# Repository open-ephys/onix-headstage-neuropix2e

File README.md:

# ONIX Neuropixels 2.0 Headstage

Serialized, multifunction ONIX headstage for IMEC Neuropixels-2.0 probes

**Features**
- 2x [Neuropixels 2.0](https://www.neuropixels.org/) probes per headstage
- Integrated absolute orientation tracking
- Single, 0.3 mm diameter micro-coaxial tether
- Torque-free commutation when used with an [ONIX Commutator](https://github.com/open-ephys/onix-commutator)
- 0.64 grams

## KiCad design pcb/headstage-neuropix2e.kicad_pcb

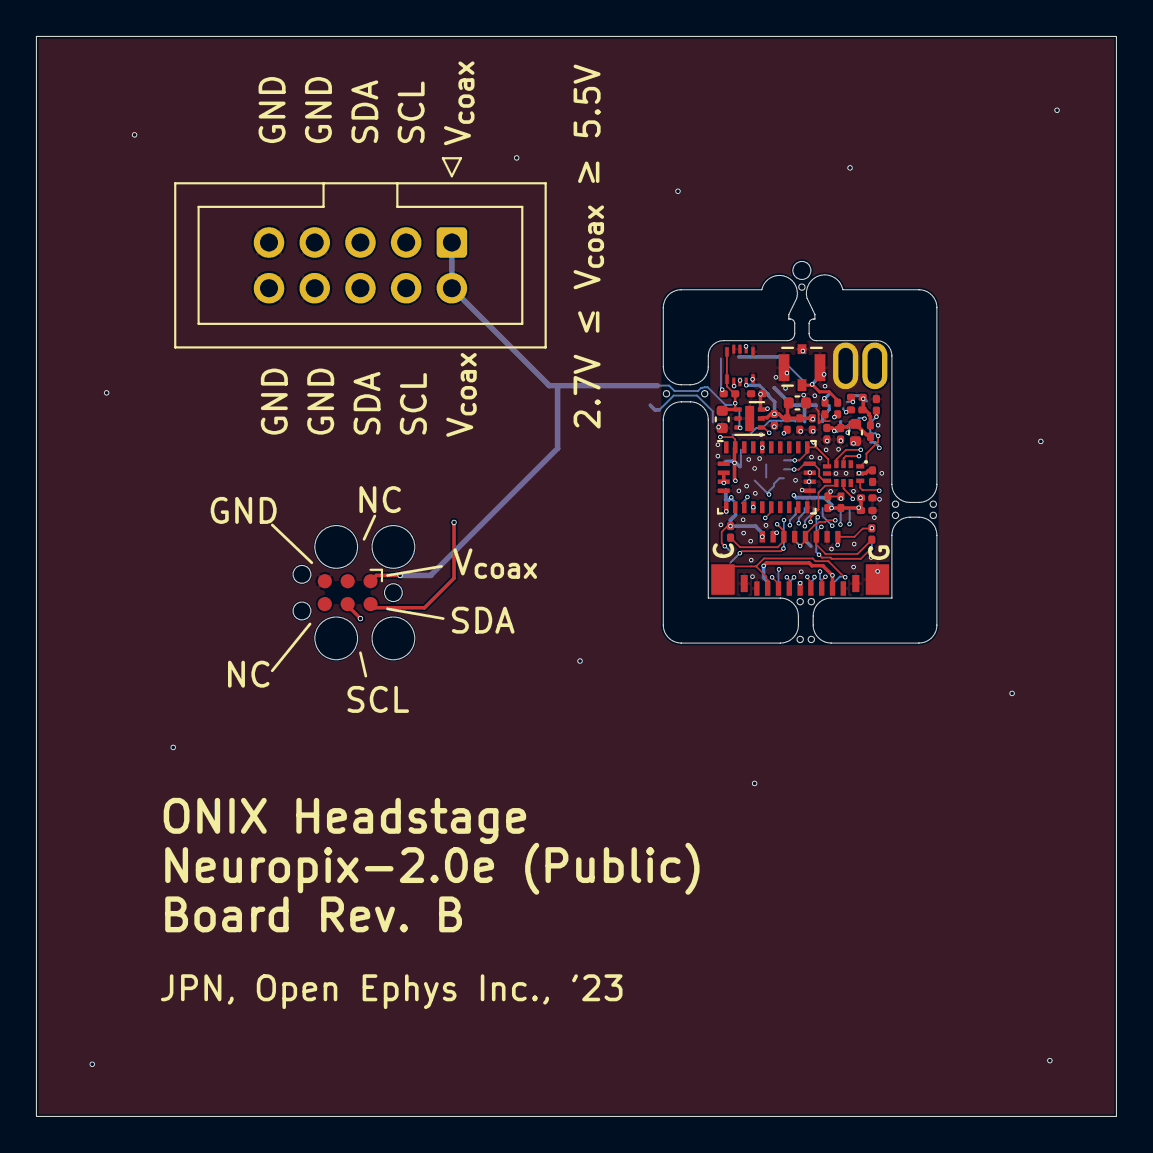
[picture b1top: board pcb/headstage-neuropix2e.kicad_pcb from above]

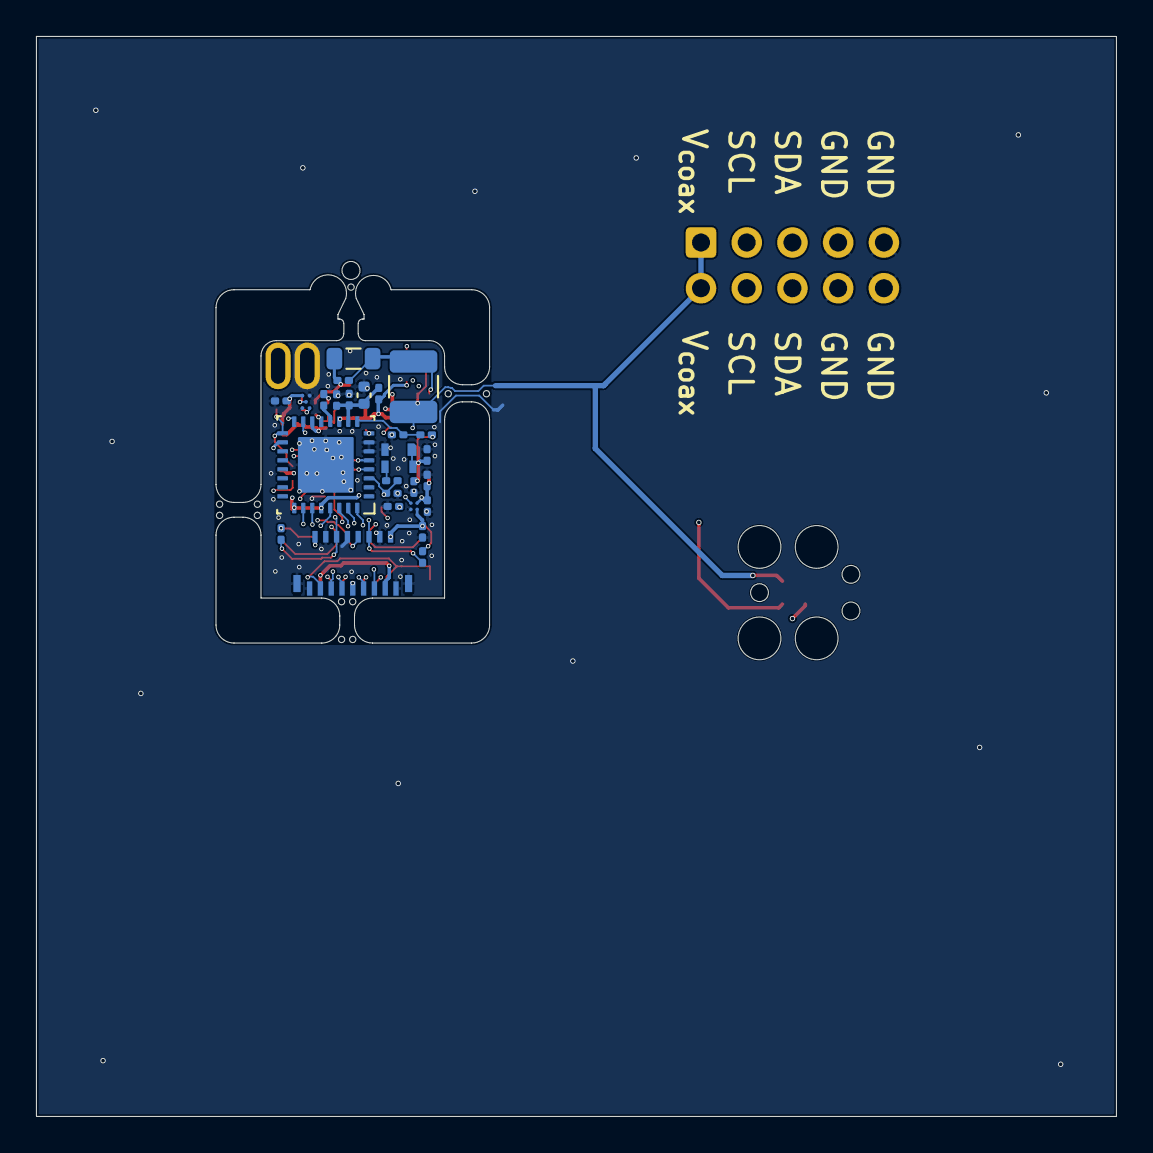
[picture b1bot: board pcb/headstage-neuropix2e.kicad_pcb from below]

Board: 4 copper layers, 60.0 x 60.0 mm, 62 parts (26 on the bottom side), 35 nets.

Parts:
C1, C2, C4, C5, C21: 1uF; C_0201_0603Metric
C3, C12, C15, C18: 10uF; C_0402_1005Metric
C6, C8, C10, C13, C16, C23: 10nF; C_0201_0603Metric
C7, C9, C11, C14, C17, C19, C22, C25, C26, C27, C28: 0.1uF; C_0201_0603Metric
C20: 47nF; C_0201_0603Metric
C24: 27pF; C_0201_0603Metric
J1: X.FL-R-SMT-1(02); HIROSE_X.FL-R-SMT-1
J2, J3: FH35C-17S-0.3SHW(99); HIROSE_FH35C-17S-0.3SHW(99)
J4: SBH11-PBPC-D05-ST-BK; IDC-Header_2x05_P2.54mm_Vertical
J5: TC2030; Tag-Connect_TC2030-IDC-FP_2x03_P1.27mm_Vertical
J6: 050700622; MOLEX_5050700622
L1: CBC3225T101MR; L_1210_3225Metric
L2: ASMPH-0805-4R7M-T; L_0805_2012Metric
L3, L4: BLF03RD501GZED; L_0201_0603Metric
R1, R2: 1k; R_0201_0603Metric
R3, R4: 2k; R_0201_0603Metric
R5, R6, R7, R9, R10, R11, R12: 10k; R_0201_0603Metric
R8: 49.9; R_0201_0603Metric
R13: 10; R_0201_0603Metric
TP1: GND; OE_TP-Oval-2.8x1.6mm
TP2: NP_{Lesion}; OE_TP-Oval-2.8x1.6mm
TP3: NP_{Cal}; TestPoint_Pad_1.3x1.7mm_Tight
TP4: NP_{TP1}; TestPoint_Pad_1.3x1.7mm_Tight
U1: MIC5335-JGYMT; MICROCHIP_TDFN-6-1EP_1.6x1.6mm_P0.5mm_EP0.5x1.4mm
U2: NCP163AFCT180T2G; ONSEMI_567JZ_WLCSP4-0.64x0.64
U3: DS90UB933TRTVTQ1; TI_RTV0032A
U4: STG3856; ST_QFN12L_2.2x1.4x0.55mm_P0.4mm
U5: ECS-2016MV-480-CN-TR; MICROCHIP_VFLGA4-2.0x1.6
U6: M24C64-FCS6TP/K; ST_WLCSP5-0.959x1.073
U7: BNO055; LGA-28_5.2x3.8mm_P0.5mm

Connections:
+1.8VA: C4.1, J2.2, J2.3, J2.16, J3.2, J3.3, J3.16, R9.1, R10.1, R11.1, R12.1, U2.A2 (VOUT)
+1V8: C1.1, C6.1, C7.1, C8.1, C9.1, C13.1, C14.1, C15.1, C22.1, C23.1, C25.2, C27.2, J6.5, L3.2, L4.2, R1.1, R2.1, R6.1, R7.1, U1.5 (VOUT2), U3.11 (VDDT), U3.25 (VDDIO), U3.28 (VDDD), U4.11 (VCC), U5.1 (EN), U5.4 (VCC), U6.A1 (VCC), U7.28 (VDDIO)
+2V5: C2.1, C5.1, C26.2, J6.6, U1.6 (VOUT1), U2.A1 (VIN), U7.3 (VDD), U7.4 (~BOOT_LOAD_PIN), U7.11 (~RESET)
+4V: C3.1, J4.1, J4.2, J5.1 (VCC), J6.MP1 (MountPin1), J6.MP2 (MountPin2), L1.1, R3.1, U1.1 (VIN), U1.3 (EN2), U1.4 (EN1)
/DC Tap & Regulation/RF+DC: C19.2, J1.1 (In), L2.1, R4.2
/DC Tap & Regulation/VDDA_{EN}: U2.B1 (EN), U3.15 (GPIO0)
/Neuropixels 2.0/D0_{A}: J2.5, U3.26 (DIN_6)
/Neuropixels 2.0/D0_{B}: J3.5, U3.32 (DIN_11)
/Neuropixels 2.0/D1_{A}: J2.11, U3.31 (DIN_10)
/Neuropixels 2.0/D1_{B}: J3.11, U3.27 (DIN_7)
/Neuropixels 2.0/D2_{A}: J2.7, U3.29 (DIN_8)
/Neuropixels 2.0/D2_{B}: J3.7, U3.30 (DIN_9)
/Neuropixels 2.0/NP_{Cal}: J2.15, J3.15, TP3.1
/Neuropixels 2.0/NP_{Lesion}: J2.13, J3.13, TP2.1
/Neuropixels 2.0/NP_{Sel0}: R5.1, U3.17 (GPIO2/CLK0), U4.12 (IN1)
/Neuropixels 2.0/NP_{Sel1}: U3.18 (GPIO3/CLKIN), U4.10 (IN2)
/Neuropixels 2.0/NP_{~RST}: J2.8, J3.8, U3.16 (GPIO1)
/Neuropixels 2.0/PCLK: C24.1, J2.9, J3.9, R13.2, U3.3 (PCLK)
/Neuropixels 2.0/SCL: J4.3, J4.4, J5.4 (SWCLK), J6.1, R2.2, U3.4 (SCL), U4.6 (D2), U6.C3 (SCL), U7.19 (COM1)
/Neuropixels 2.0/SCL_{A}: J2.6, R11.2, U4.8 (2S2)
/Neuropixels 2.0/SCL_{B}: J3.6, R12.2, U4.7 (2S3)
/Neuropixels 2.0/SDA: J4.5, J4.6, J5.2 (SWDIO), J6.3, R1.2, U3.5 (SDA), U4.4 (D1), U6.B2 (SDA), U7.20 (COM0)
/Neuropixels 2.0/SDA_{A}: J2.12, R9.2, U4.2 (1S2)
/Neuropixels 2.0/SDA_{B}: J3.12, R10.2, U4.3 (1S3)
/Serializer/Dout-: C20.2, R8.1
GND: C1.2, C2.2, C3.2, C4.2, C5.2, C6.2, C7.2, C8.2, C9.2, C10.2, C11.2, C12.2, C13.2, C14.2, C15.2, C16.2, C17.2, C18.2, C21.2, C22.2, C23.2, C24.2, C25.1, C26.1, C27.1, C28.1, J1.2 (Ext), J2.1, J2.4, J2.10, J2.14, J2.17, J2.MP (MountPin), J3.1, J3.4, J3.10, J3.14, J3.17, J3.MP (MountPin), J4.7, J4.8, J4.9, J4.10, J5.5 (GND), J6.2, J6.4, J6.MP3 (MountPin3), J6.MP4 (MountPin4), R5.2, R8.2, TP1.1, TP4.1, U1.2 (GND), U1.7 (GND), U2.B2 (GND), U3.6 (ID[X]), U3.7 (RES), U3.33 (GND(DAP)), U4.5 (GND), U5.2 (GND), U6.A3 (VSS), U6.C1 (~WC), U7.2 (GND), U7.5 (PS1), U7.6 (PS0), U7.15 (GNDIO), U7.16 (GNDIO), U7.17 (COM3), U7.18 (COM2), U7.25 (GNDIO)
unnamed: C10.1, C11.1, C12.1, L3.1, U3.10 (VDDPLL)
unnamed: C16.1, C17.1, C18.1, L4.1, U3.14 (VDDCML)
unnamed: L1.2, L2.2, R3.2, R4.1
unnamed: C20.1, U3.12 (DOUTN)
unnamed: C19.1, U3.13 (DOUTP)
unnamed: R7.2, U3.8 (MODE)
unnamed: C21.1, R6.2, U3.9 (PDB)
unnamed: R13.1, U5.3 (OUT)
unnamed: C28.2, U7.9 (CAP)

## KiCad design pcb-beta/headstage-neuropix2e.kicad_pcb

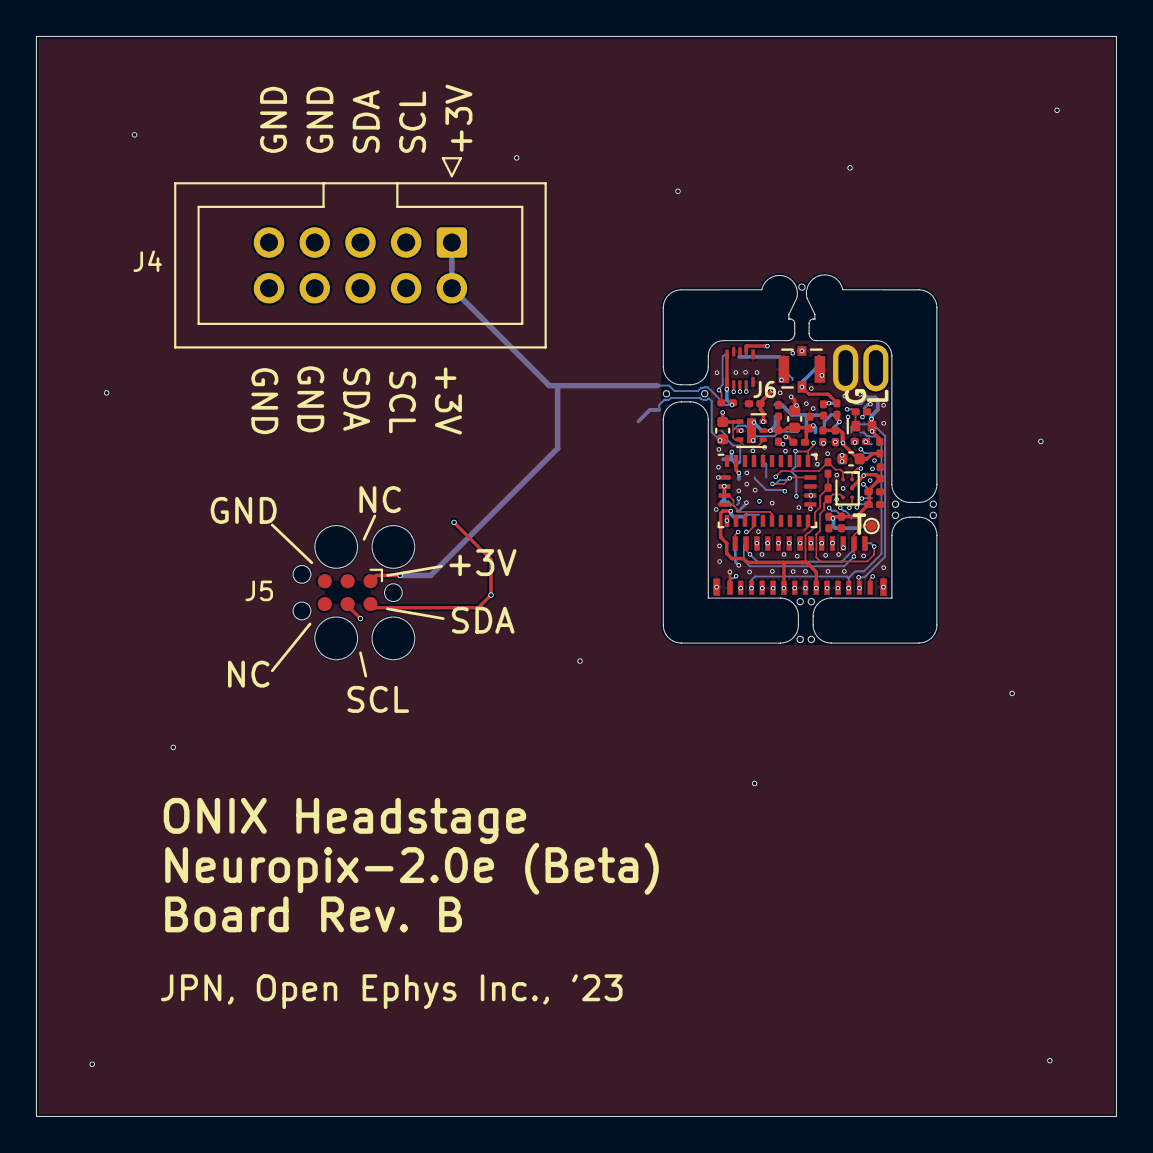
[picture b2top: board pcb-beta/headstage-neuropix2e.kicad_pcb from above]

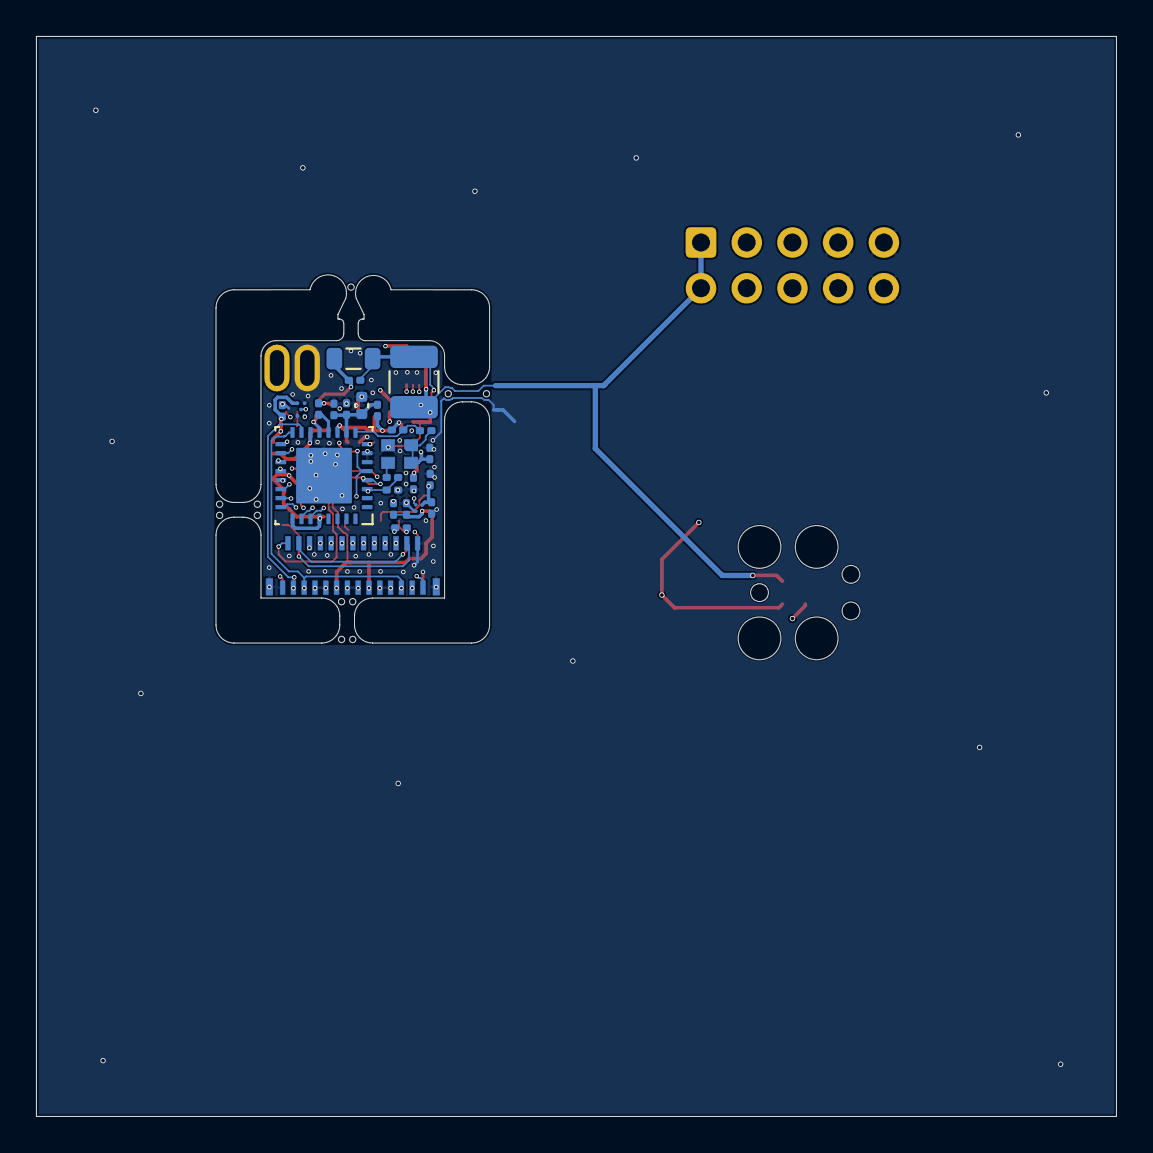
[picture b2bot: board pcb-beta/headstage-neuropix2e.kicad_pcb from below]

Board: 4 copper layers, 60.0 x 60.0 mm, 60 parts (25 on the bottom side), 36 nets.

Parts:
C1, C2, C4, C5, C21: 1uF; C_0201_0603Metric
C3, C12, C15, C18: 10uF; C_0402_1005Metric
C6, C8, C10, C13, C16, C23: 10nF; C_0201_0603Metric
C7, C9, C11, C14, C17, C19, C22, C25, C26, C27, C28: 0.1uF; C_0201_0603Metric
C20: 47nF; C_0201_0603Metric
C24: 27pF; C_0201_0603Metric
D1: SML-P11UTT86R; ROHM_SML-P11MTT86R
J1: X.FL-R-SMT-1(02); HIROSE_X.FL-R-SMT-1
J2, J3: 046844727002846+; KYOCERA_046844727002846+
J4: SBH11-PBPC-D05-ST-BK; IDC-Header_2x05_P2.54mm_Vertical
J5: TC2030; Tag-Connect_TC2030-IDC-FP_2x03_P1.27mm_Vertical
J6: 050700622; MOLEX_5050700622
L1: CBC3225T101MR; L_1210_3225Metric
L2: ASMPH-0805-4R7M-T; L_0805_2012Metric
L3, L4: BLF03RD501GZED; L_0201_0603Metric
R1, R2: 2k; R_0201_0603Metric
R3, R9, R10, R11: 1k; R_0201_0603Metric
R4, R5, R6: 10k; R_0201_0603Metric
R7: 49.9; R_0201_0603Metric
R12: 22; R_0201_0603Metric
TP1: GND; OE_TP-Oval-2.8x1.6mm
TP2: NP_{TP0}; OE_TP-Oval-2.8x1.6mm
TP3: NP_{TP1}; TestPoint_Pad_D0.6mm
U1: MIC5335-JGYMT; MICROCHIP_TDFN-6-1EP_1.6x1.6mm_P0.5mm_EP0.5x1.4mm
U2: NCP163AFCT180T2G; ONSEMI_567JZ_WLCSP4-0.64x0.64
U3: DS90UB933TRTVTQ1; TI_RTV0032A
U4: TS5A3159AYZPR; TI_YZP0006
U5: ECS-2016MV-480-CN-TR; ECS_2016MV
U6: M24C64-FCS6TP/K; ST_WLCSP5-0.959x1.073
U7: BNO055; LGA-28_5.2x3.8mm_P0.5mm

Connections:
+1.8VA: C4.1, J2.11, J2.17, J3.11, J3.17, R9.1, R10.1, R11.1, U2.A2 (VOUT)
+1V8: C1.1, C6.1, C7.1, C8.1, C9.1, C13.1, C14.1, C15.1, C22.1, C23.1, C25.2, C27.2, D1.2 (A), J6.5, L3.2, L4.2, R5.1, R6.1, U1.5 (VOUT2), U2.B1 (EN), U3.11 (VDDT), U3.25 (VDDIO), U3.28 (VDDD), U4.B2 (V+), U5.1 (EN), U5.4 (VCC), U6.A1 (VCC), U7.28 (VDDIO)
+2V5: C2.1, C5.1, C26.2, J6.6, U1.6 (VOUT1), U2.A1 (VIN), U7.3 (VDD), U7.4 (~BOOT_LOAD_PIN), U7.11 (~RESET)
+4V: C3.1, J4.1, J4.2, J5.1 (VCC), J6.MP1 (MountPin1), J6.MP2 (MountPin2), L1.1, R1.1, U1.1 (VIN), U1.3 (EN2), U1.4 (EN1)
/DC Tap & Regulation/RF+DC: C19.2, J1.1 (In), L2.1, R2.2
/Neuropixels 2.0/D0: J2.22, J3.6, U3.19 (DIN_0)
/Neuropixels 2.0/D1: J2.20, J3.8, U3.20 (DIN_1)
/Neuropixels 2.0/D2: J2.18, J3.10, U3.21 (DIN_2)
/Neuropixels 2.0/D3: J2.16, J3.12, U3.22 (DIN_3)
/Neuropixels 2.0/D4: J2.12, J3.16, U3.23 (DIN_4)
/Neuropixels 2.0/D5: J2.10, J3.18, U3.24 (DIN_5)
/Neuropixels 2.0/D6: J2.8, J3.20, U3.26 (DIN_6)
/Neuropixels 2.0/D7: J2.6, J3.22, U3.27 (DIN_7)
/Neuropixels 2.0/NP_{Select}: R4.1, U3.17 (GPIO2/CLK0), U4.A2 (IN)
/Neuropixels 2.0/NP_{TP0}: J2.27, J3.27, TP2.1
/Neuropixels 2.0/NP_{TP1}: J2.24, J3.24, TP3.1
/Neuropixels 2.0/NP_{~MUXRST}: J2.5, J2.23, J3.5, J3.23, U3.16 (GPIO1)
/Neuropixels 2.0/NP_{~RST}: J2.3, J2.25, J3.3, J3.25, U3.15 (GPIO0)
/Neuropixels 2.0/PCLK: C24.1, J2.14, J3.14, R12.2, U3.3 (PCLK)
/Neuropixels 2.0/SCL: J2.4, J3.4, J4.3, J4.4, J5.4 (SWCLK), J6.1, R11.2, U3.4 (SCL), U6.C3 (SCL), U7.19 (COM1)
/Neuropixels 2.0/SDA: J4.5, J4.6, J5.2 (SWDIO), J6.3, U3.5 (SDA), U4.C2 (COM), U6.B2 (SDA), U7.20 (COM0)
/Neuropixels 2.0/SDA_{A}: J2.2, R9.2, U4.A1 (NO)
/Neuropixels 2.0/SDA_{B}: J3.2, R10.2, U4.C1 (NC)
/Serializer/Dout-: C20.2, R7.1
GND: C1.2, C2.2, C3.2, C4.2, C5.2, C6.2, C7.2, C8.2, C9.2, C10.2, C11.2, C12.2, C13.2, C14.2, C15.2, C16.2, C17.2, C18.2, C21.2, C22.2, C23.2, C24.2, C25.1, C26.1, C27.1, C28.1, J1.2 (Ext), J2.1, J2.7, J2.9, J2.13, J2.15, J2.19, J2.21, J2.26, J2.MP (MountPin), J3.1, J3.7, J3.9, J3.13, J3.15, J3.19, J3.21, J3.26, J3.MP (MountPin), J4.7, J4.8, J4.9, J4.10, J5.5 (GND), J6.2, J6.4, J6.MP3 (MountPin3), J6.MP4 (MountPin4), R4.2, R7.2, TP1.1, U1.2 (GND), U1.7 (GND), U2.B2 (GND), U3.6 (ID[X]), U3.7 (RES), U3.33 (GND(DAP)), U4.B1 (GND), U5.2 (GND), U6.A3 (VSS), U6.C1 (~WC), U7.2 (GND), U7.5 (PS1), U7.6 (PS0), U7.15 (GNDIO), U7.16 (GNDIO), U7.17 (COM3), U7.18 (COM2), U7.25 (GNDIO)
unnamed: C10.1, C11.1, C12.1, L3.1, U3.10 (VDDPLL)
unnamed: C16.1, C17.1, C18.1, L4.1, U3.14 (VDDCML)
unnamed: D1.1 (K), R3.1
unnamed: L1.2, L2.2, R1.2, R2.1
unnamed: C20.1, U3.12 (DOUTN)
unnamed: C19.1, U3.13 (DOUTP)
unnamed: R3.2, U3.18 (GPIO3/CLKIN)
unnamed: R6.2, U3.8 (MODE)
unnamed: C21.1, R5.2, U3.9 (PDB)
unnamed: R12.1, U5.3 (OUT)
unnamed: C28.2, U7.9 (CAP)

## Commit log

2023-02-23 Initial commit
    - Schematic: No FPGA, onboard EEPROM and BNO055 via software controlled
    I2C.
    - Rough component placement, subject to change.
2023-02-26 Inital routing complete
    - Addressed Aaron's review
    - Pullup on output side of analog switch to prevent floating SDA
    - Other minor changes
2023-03-01 Address team comments
    - Add extra mouse-bite supports
    - Enbiggen cable strain relief spear
    - Add DNP 0.1" header for bench debug
    - Small routing changes
    - Update and complete BOM
2023-03-09 Updates to design after feedback from assembler
    - Replace obsolete TE_2013496-9 ZIF connector used by IMEC with
    046844727002846+, which should fit NP 2.0 flex connectors (see design
    folder for comparison). We will see.
    - Replaced programmable MEMS oscillator with standard quartz since this
    is a common frequency.
    - Other BOM updates to account for obsolete or out of stock components
2023-03-09 Forgot to update BOM in last commit
2023-09-13 Move pcb to pcb-beta directory
    - Because this board only works with Beta-test NP2.0 probes
2023-09-13 Add headstage for public NP2.0 probe
    - Uses a completely different ZIF connector and bus architecture
2023-09-14 Revision B (Beta)
    - Neuropixels 2.0 headstage for beta-test probes
    - Updated PCB specs to match the headstage for publically avaiable
    probes (increase via size to 0.25/0.15)
2023-09-15 Rev. A of public version of headstage
    - Being fabricated for testing
2023-09-15 Fix dirll and component origin
2023-09-15 Rev. B of beta-test variant
    - This was sent for fabrication
2023-10-05 Revision A
    - This design was sent to fab
2023-11-09 Revision B
    - Fix incorrect STG3856 symbol and make corresponding changes to PCB
    - Flip bits 1 and 2 in probe interaces (fixes #1)
    - Improve silkscreen
2023-11-11 Changed debug's (J4) attribute to be excluded from the BOM.
2023-11-11 Changed programming's (J5) attribute to DNP.
2023-11-11 Changed expansion's (J6) attribute to be part of the BOM.
2023-11-11 Added new fields (OEPS PN, MPN, and Type) to all components.
2023-11-11 Corrected MPN of J6.
2023-12-07 Bring changes on schematic over to board file.
2023-12-14 Add json files for EEPROM generation
2024-04-29 Update README.md
    - Add headstage weight
